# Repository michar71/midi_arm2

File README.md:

# midi_arm2

## BABOI Update
1) Download .bin Firmware File
1) Power Up BABOI
2) Connect Computer o Phone to BABOI Access Point
3) Go to webapge 192.168.1.1 in browser
4) Select "Update"
5) Select firmware File

##Processing Sketch update
Just copy the .app file in the relase folder to your computer 

## LED's

**Left LED**

Red,Green,Blue -> Boot
Yellow -> Ready for Connection
Green -> Connection initiated

**Right LED**

Off > Not Connected
Red > Pause
Green > Live
Blue > Acc/Gyro Cal
Cyan > Mag Cal
Magenta > Button Cal
White > Glove Tension Strip Cal

## Buttons

**Left**

CTRL-Button
Short Press > Live/Pause Toggle
Long Press > Gyro/Accelerometer Calibration
Very Long Press > Mag Calibration

**Front**

A-Button

**Right**

B-Button

## Calibration
- Best Way to calibrate is from the webpage
- Buttons might not work correctly initially. Calibrate from Webpage...
- Gyro/Accelerometer Calibration can be triggered both by 3 sec button press or webpage.
- Button/Mag calibration can only be triggered from webpage.
- If in doubt reset settings from webpage... (That will force a button recalibration on next start...)

## Network
- Enable Network support in App
- Connect computer to "BABOI" access point
- Web Page is available at 192.168.1.1
- VPN/Firewall might enterfere. Traffic is on Port 2255. Connection is established via Broadcast, then communication switches to unicast.

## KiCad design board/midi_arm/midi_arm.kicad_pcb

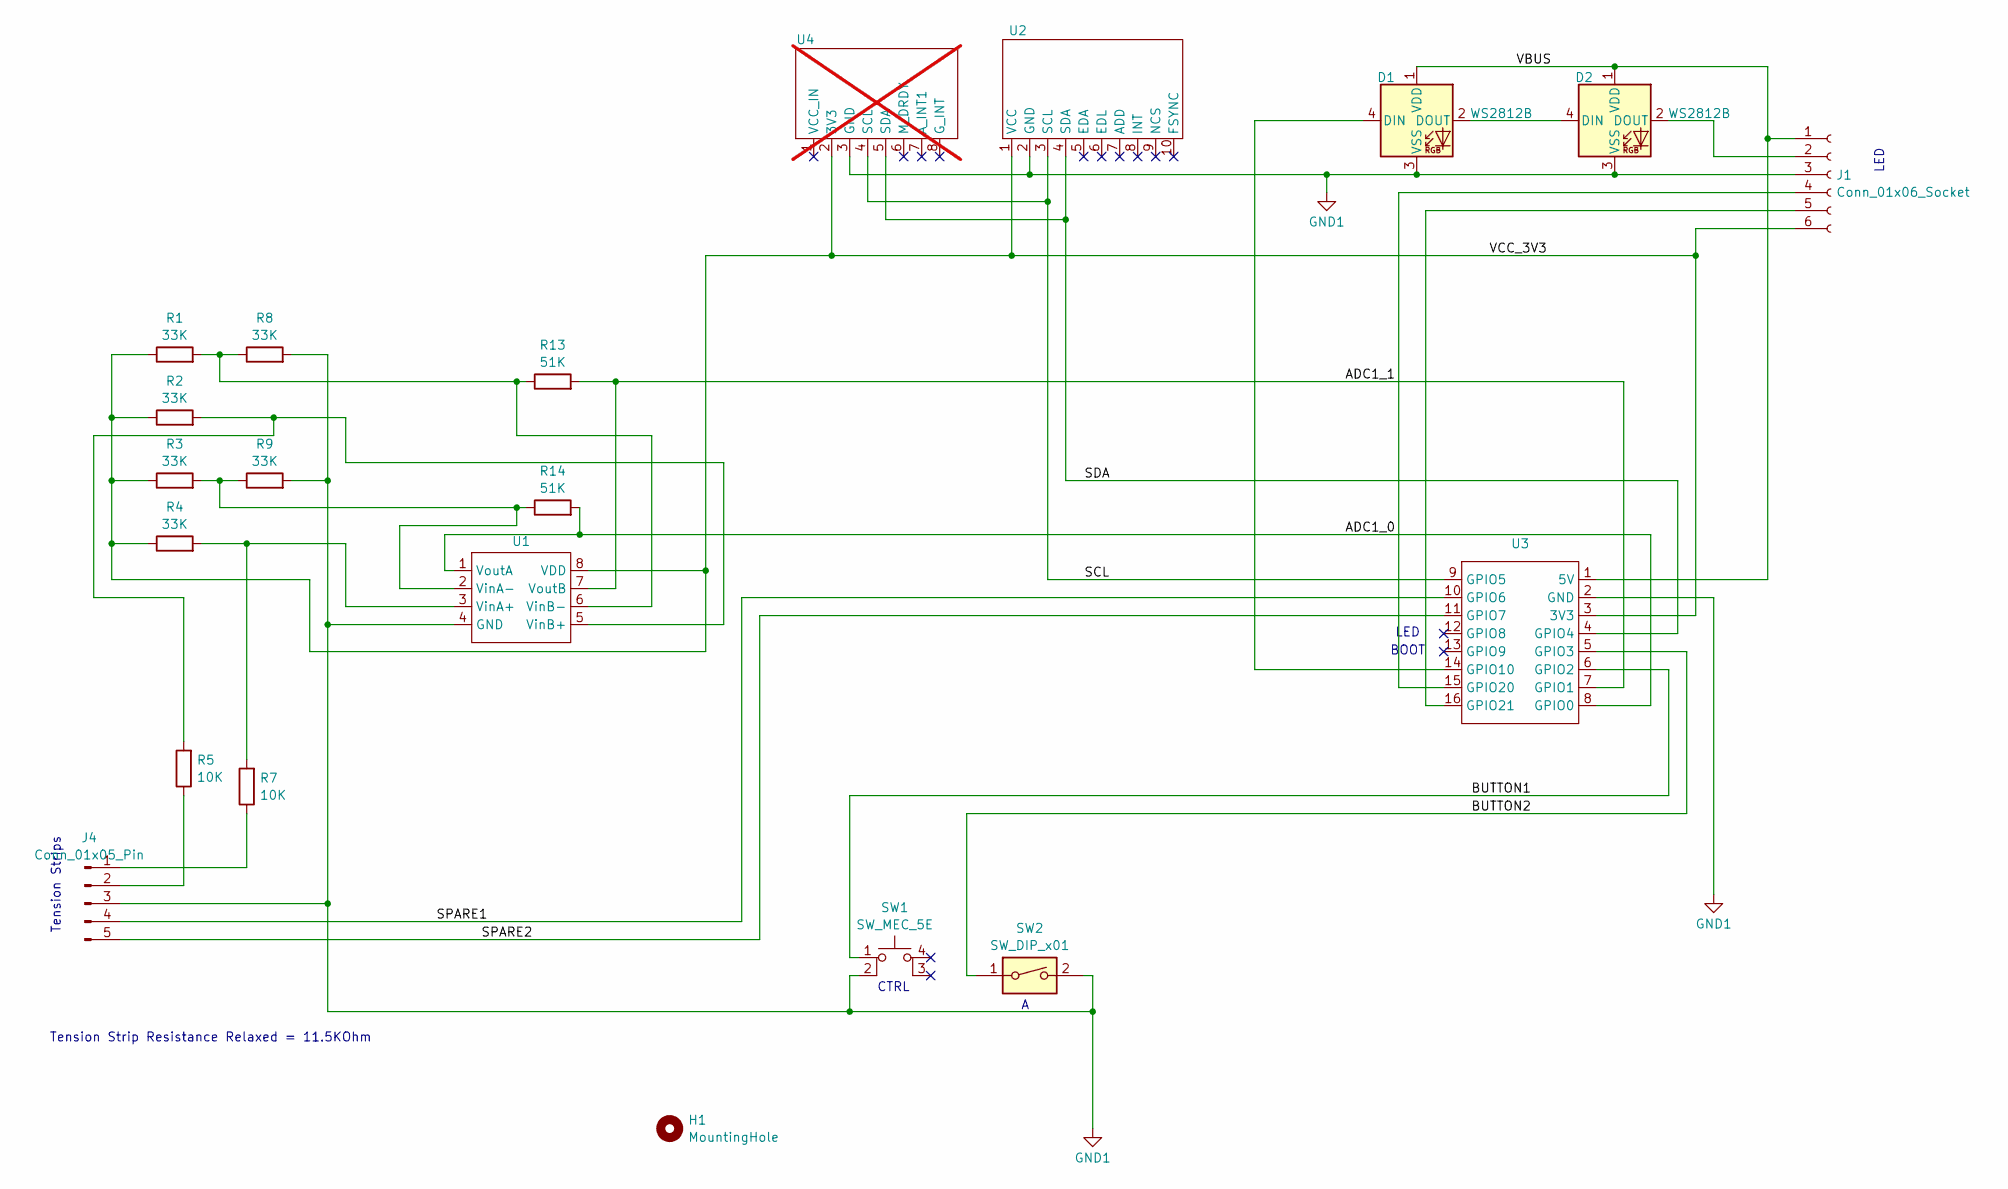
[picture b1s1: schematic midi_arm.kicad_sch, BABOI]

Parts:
D1, D2: WS2812B; LED_WS2812B_PLCC4_5.0x5.0mm_P3.2mm
H1: MountingHole; MountingHole_2mm
J1: Conn_01x06_Socket; PinHeader_1x06_P2.54mm_Vertical
J4: Conn_01x05_Pin; PinHeader_1x05_P2.54mm_Vertical
R1, R2, R3, R4, R8, R9: 33K; R_0805_2012Metric_Pad1.20x1.40mm_HandSolder
R5, R7: 10K; R_0805_2012Metric_Pad1.20x1.40mm_HandSolder
R13, R14: 51K; R_0805_2012Metric_Pad1.20x1.40mm_HandSolder
SW1: SW_MEC_5E; SW_Push_SMD
SW2: SW_DIP_x01; SW_Push_SPST_NO_Alps_SKRK
U1: SOIC-8_3.9x4.9mm_P1.27mm
U2: 9250_MOD
U3: ESP32-C3_SuperMini
U4: GY-85; not fitted

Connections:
/ADC1_0: R14.2, U1.1 (VoutA), U3.8 (GPIO0)
/ADC1_1: R13.2, U1.7 (VoutB), U3.7 (GPIO1)
/BUTTON1: SW1.1, U3.6 (GPIO2)
/BUTTON2: SW2.1, U3.5 (GPIO3)
/SCL: U2.3 (SCL), U3.9 (GPIO5), U4.4 (SCL)
/SDA: U2.4 (SDA), U3.4 (GPIO4), U4.5 (SDA)
/SPARE1: J4.4, U3.10 (GPIO6)
/SPARE2: J4.5, U3.11 (GPIO7)
/VBUS: D1.1 (VDD), D2.1 (VDD), J1.1, U3.1 (5V)
/VCC_3V3: J1.6, R1.1, R2.1, R3.1, R4.1, U1.8 (VDD), U2.1 (VCC), U3.3 (3V3), U4.2 (3V3)
GND1: D1.3 (VSS), D2.3 (VSS), J1.3, J4.3, R8.2, R9.2, SW1.2, SW2.2, U1.4 (GND), U2.2 (GND), U3.2 (GND), U4.3 (GND)
unnamed: D1.4 (DIN), U3.14 (GPIO10)
unnamed: D1.2 (DOUT), D2.4 (DIN)
unnamed: D2.2 (DOUT), J1.2
unnamed: J1.4, U3.15 (GPIO20)
unnamed: J1.5, U3.16 (GPIO21)
unnamed: J4.1, R7.1
unnamed: J4.2, R5.1
unnamed: R4.2, R7.2, U1.3 (VinA+)
unnamed: R3.2, R9.1, R14.1, U1.2 (VinA-)
unnamed: R2.2, R5.2, U1.5 (VinB+)
unnamed: R1.2, R8.1, R13.1, U1.6 (VinB-)

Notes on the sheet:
LED
Tension Strip Resistance Relaxed = 11.5KOhm
CTRL
Tension Strips
BOOT

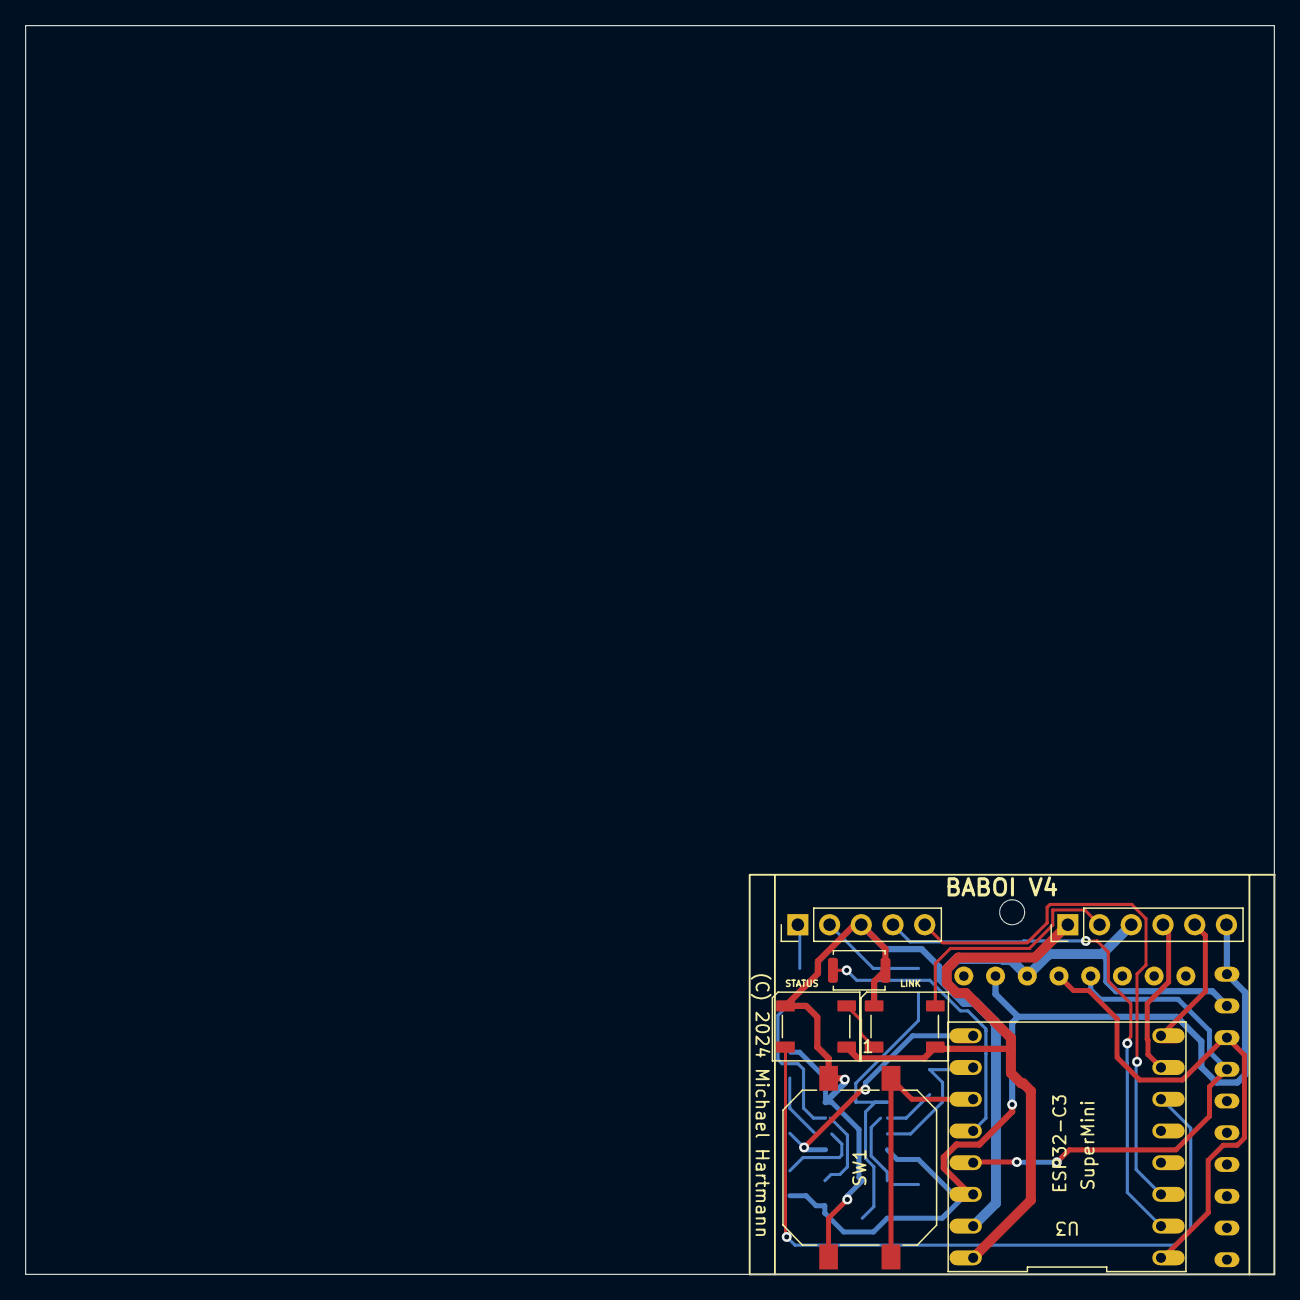
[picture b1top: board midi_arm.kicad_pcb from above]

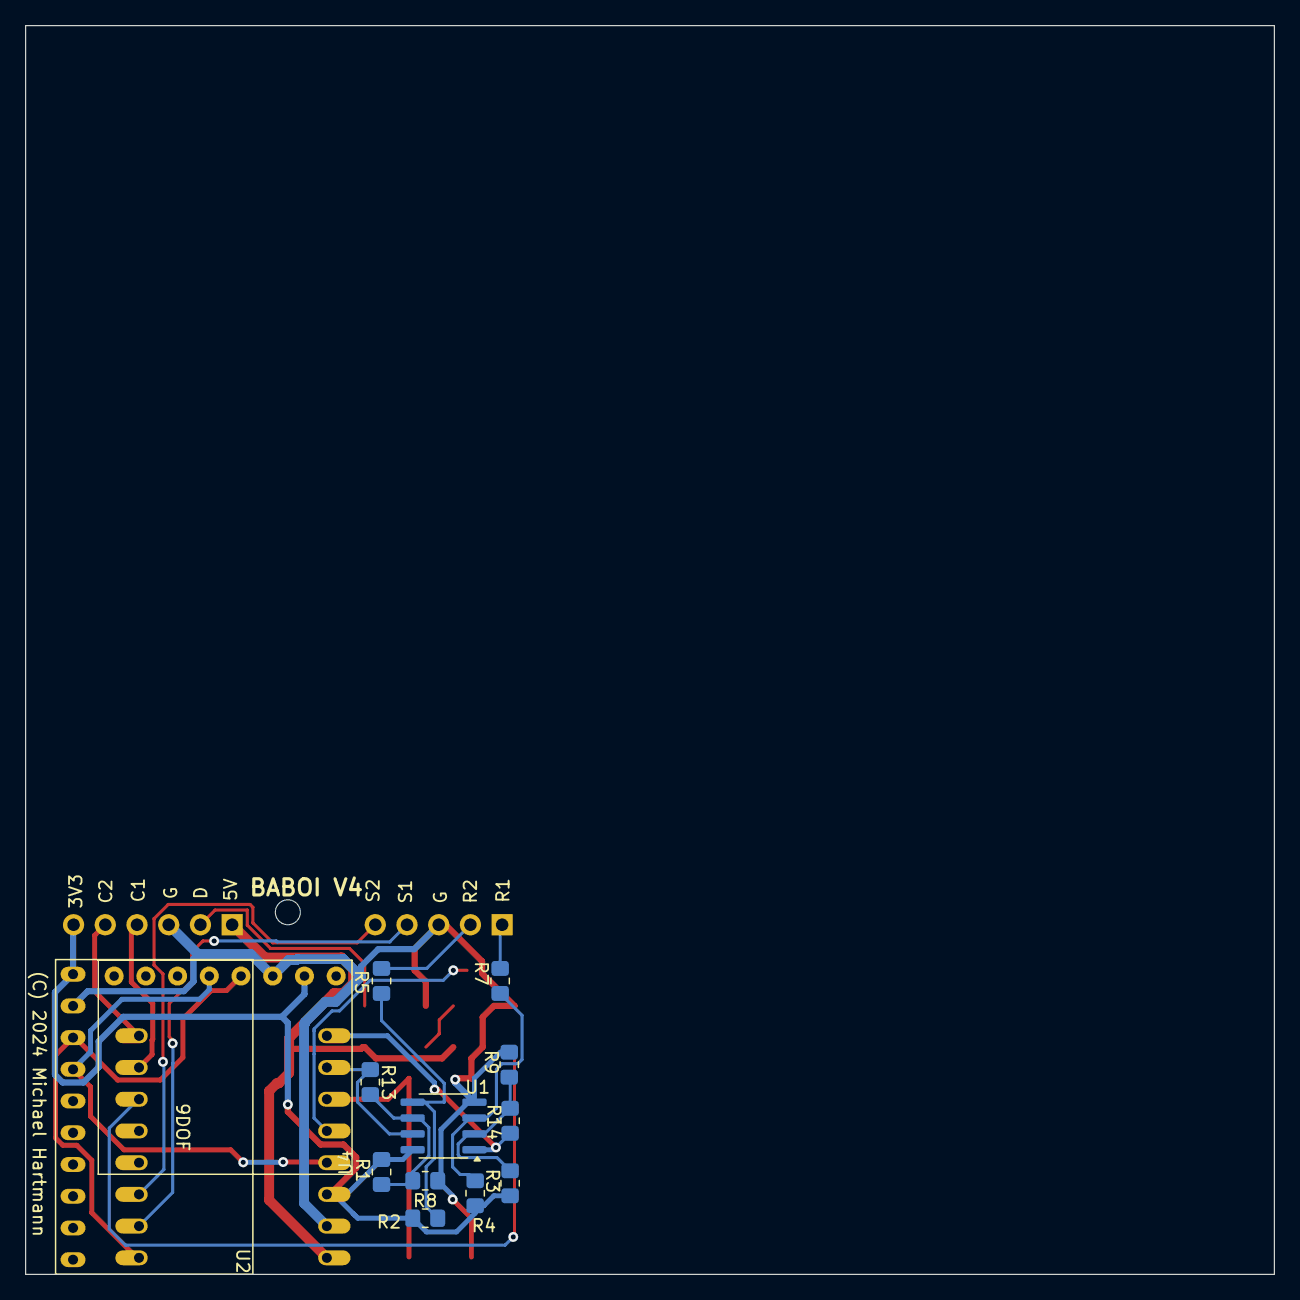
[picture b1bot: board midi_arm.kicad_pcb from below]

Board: 2 copper layers, 100.0 x 100.0 mm, 21 parts (13 on the bottom side), 22 nets.

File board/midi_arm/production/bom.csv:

Designator,Footprint,Quantity,Value,LCSC Part #
"D1_6, D1_5, D1_4, D1_3, D1_2, D1, D2_6, D2_5, D2_4, D2_3, D2_2, D2",LED_WS2812B_PLCC4_5.0x5.0mm_P3.2mm,12,WS2812B,
"J1_6, J1_5, J1_4, J1_3, J1_2, J1",PinHeader_1x06_P2.54mm_Vertical,6,Conn_01x06_Socket,
"J4_6, J4_5, J4_4, J4_3, J4_2, J4",PinHeader_1x05_P2.54mm_Vertical,6,Conn_01x05_Pin,
"R1_6, R1_5, R1_4, R1_3, R1_2, R1, R2_6, R2_5, R2_4, R2_3, R2_2, R2, R3_6, R3_5, R3_4, R3_3, R3_2, R3, R4_6, R4_5, R4_4, R4_3, R4_2, R4, R8_6, R8_5, R8_4, R8_3, R8_2, R8, R9_6, R9_5, R9_4, R9_3, R9_2, R9",0805,36,33K,
"R13_6, R13_5, R13_4, R13_3, R13_2, R13, R14_6, R14_5, R14_4, R14_3, R14_2, R14",0805,12,51K,
"R5_6, R5_5, R5_4, R5_3, R5_2, R5, R7_6, R7_5, R7_4, R7_3, R7_2, R7",0805,12,10K,
"SW1_6, SW1_5, SW1_4, SW1_3, SW1_2, SW1",SW_Push_SMD,6,SW_MEC_5E,
"SW2_6, SW2_5, SW2_4, SW2_3, SW2_2, SW2",SW_Push_SPST_NO_Alps_SKRK,6,SW_DIP_x01,
"U1_6, U1_5, U1_4, U1_3, U1_2, U1",SOIC-8_3.9x4.9mm_P1.27mm,6,~,
"U2_6, U2_5, U2_4, U2_3, U2_2, U2",9250_MOD,6,~,
"U3_6, U3_5, U3_4, U3_3, U3_2, U3",ESP32-C3_SuperMini,6,~,
"U4_6, U4_5, U4_4, U4_3, U4_2, U4",GY-85,6,~,

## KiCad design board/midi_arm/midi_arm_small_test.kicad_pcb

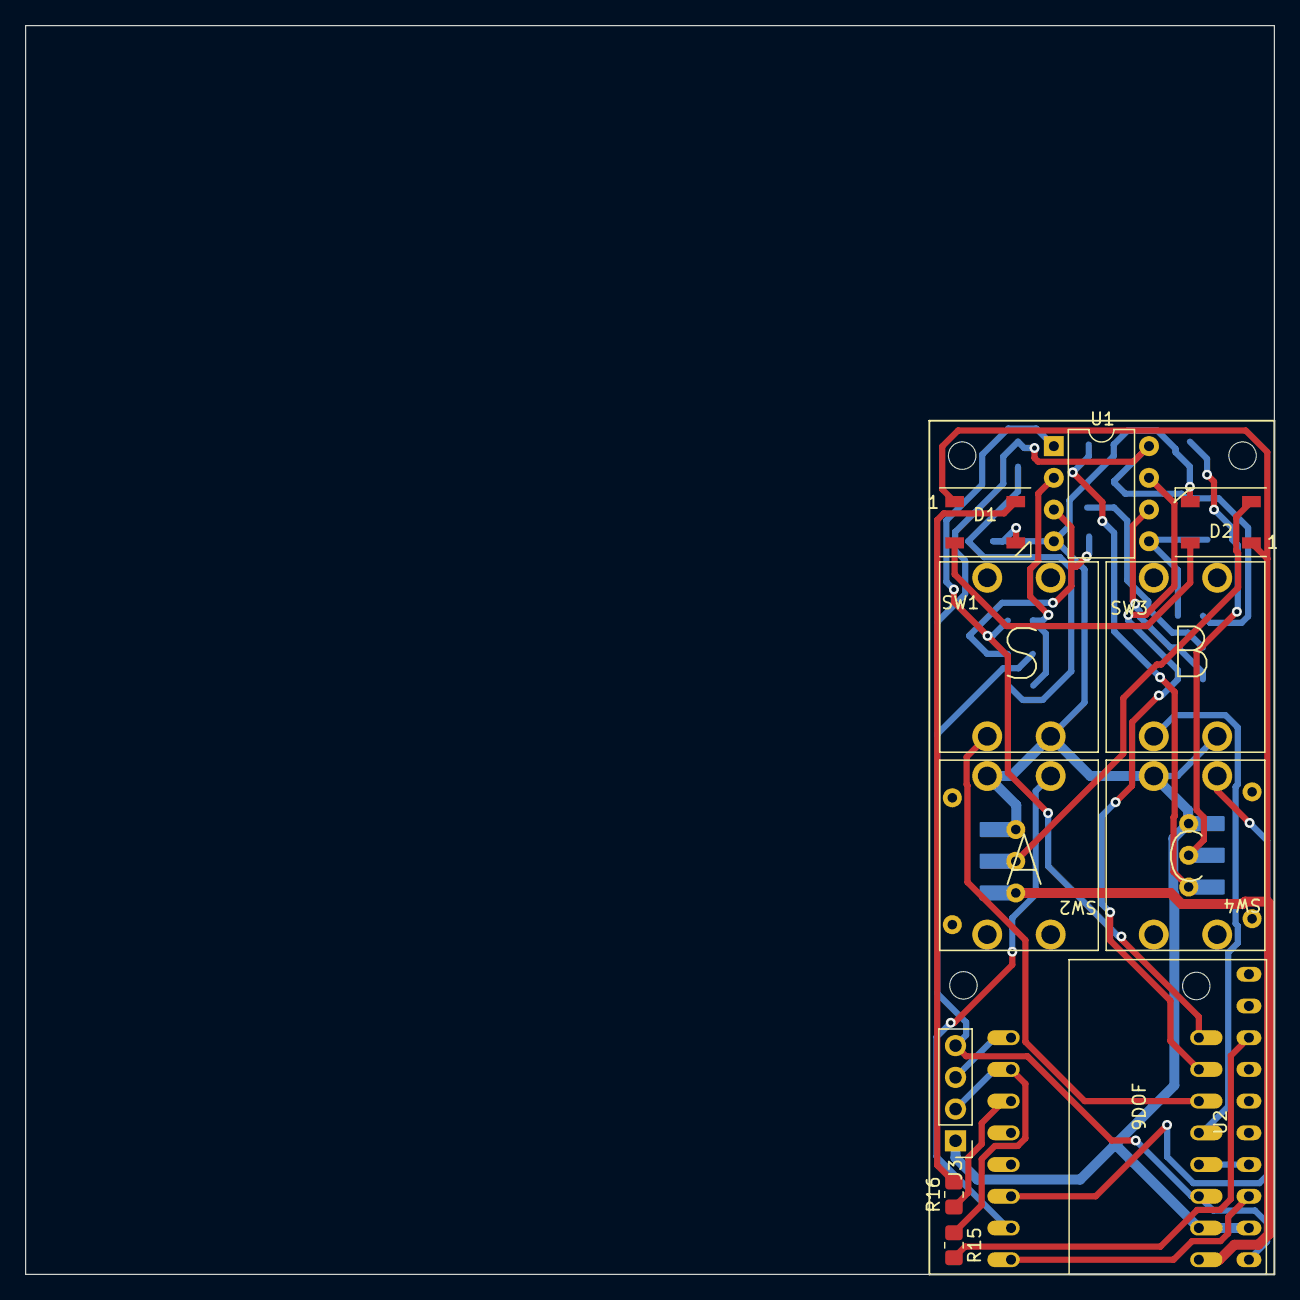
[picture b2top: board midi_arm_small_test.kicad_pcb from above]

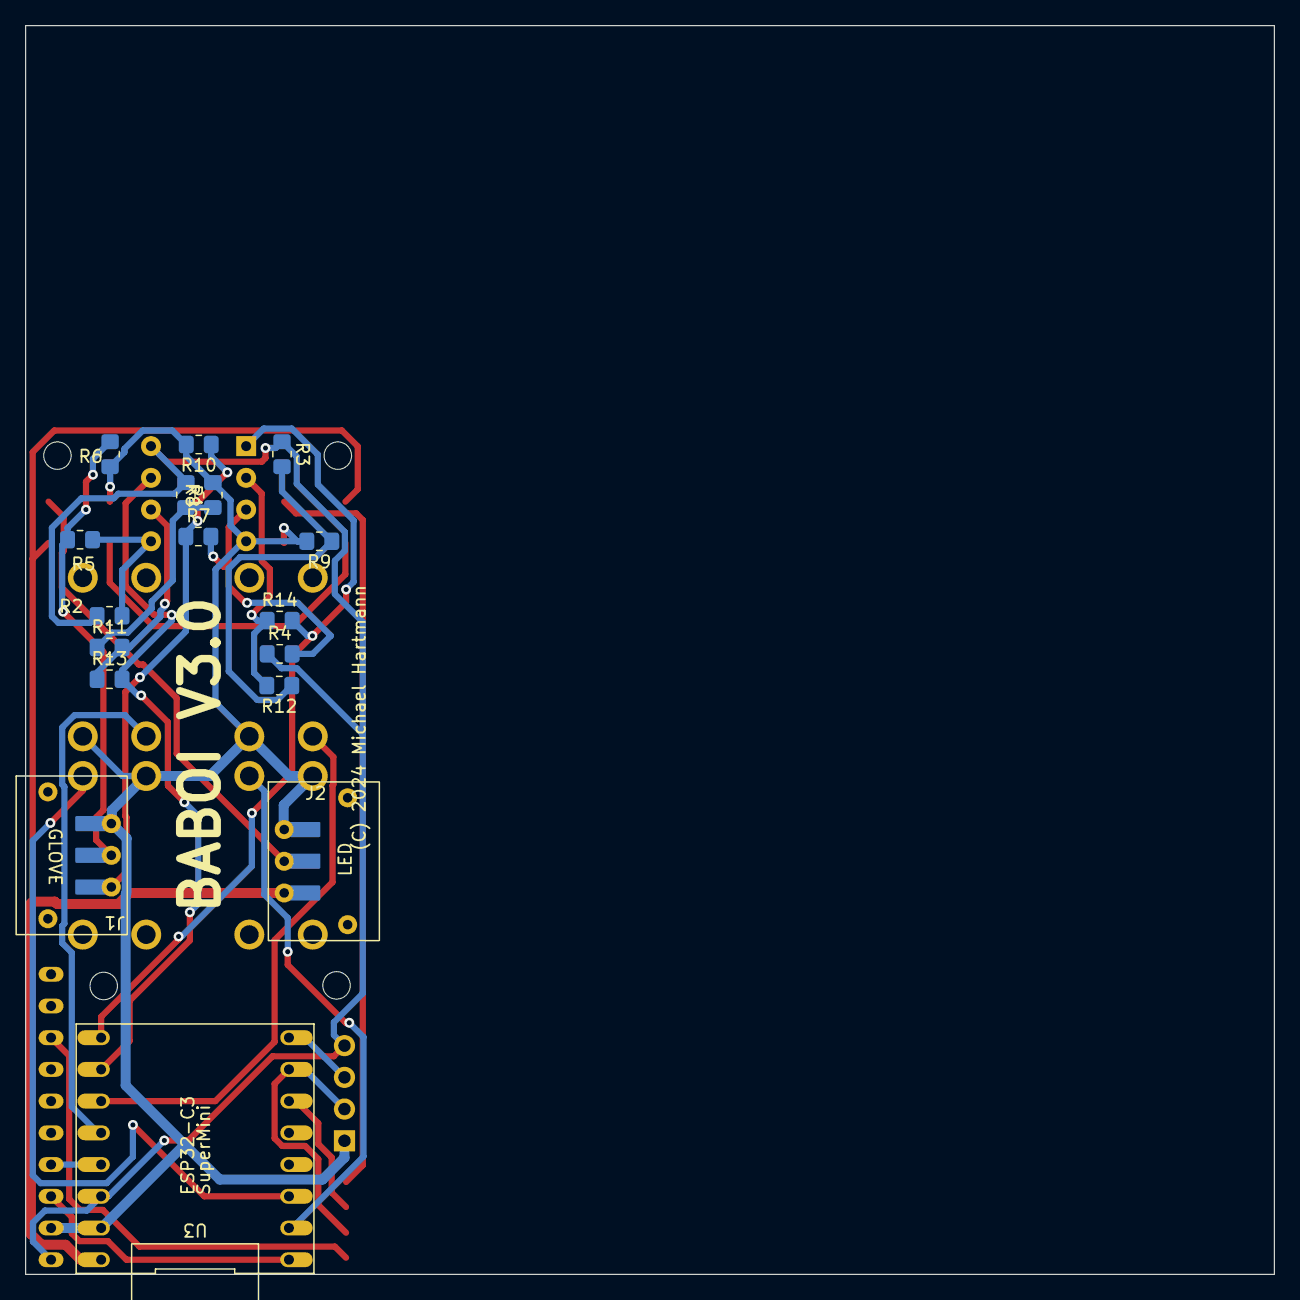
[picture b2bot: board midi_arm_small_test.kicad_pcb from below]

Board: 2 copper layers, 100.0 x 100.0 mm, 32 parts (17 on the bottom side), 26 nets.

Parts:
D1, D2: WS2812B; LED_WS2812B_PLCC4_5.0x5.0mm_P3.2mm
H1, H2, H3, H4: MountingHole; MountingHole_2.2mm_M2
J1, J2: Conn_01x03_Pin; LED_conn
J3: Conn_01x04_Pin; PinHeader_1x04_P2.54mm_Vertical
R1, R3: 2.4k; R_0805_2012Metric_Pad1.20x1.40mm_HandSolder
R2, R4: 5.1k; R_0805_2012Metric_Pad1.20x1.40mm_HandSolder
R5, R6, R7, R8, R9, R10, R11, R12: 3.3k; R_0805_2012Metric_Pad1.20x1.40mm_HandSolder
R13, R14, R15, R16: 24k; R_0805_2012Metric_Pad1.20x1.40mm_HandSolder
SW1, SW2, SW3, SW4: SW_MEC_5E; switch_Simple
U1: DIP-8_W7.62mm
U2: 9250_MOD
U3: ESP32-C3_SuperMini

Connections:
/ADC1_0: R14.2, U1.1 (VoutA), U3.8 (GPIO0)
/ADC1_1: R13.2, U1.7 (VoutB), U3.7 (GPIO1)
/BUTTON1: SW1.2, U3.6 (GPIO2)
/BUTTON2: SW3.2, U3.5 (GPIO3)
/BUTTON3: SW2.2, U3.10 (GPIO6)
/BUTTON4: SW4.2, U3.11 (GPIO7)
/SCL: U2.3 (SCL), U3.9 (GPIO5)
/SDA: U2.4 (SDA), U3.4 (GPIO4)
/VBUS: D1.1 (VDD), D2.1 (VDD), J2.3, U3.1 (5V)
/VCC_3V3: J3.4, R1.1, R2.1, R3.1, R4.1, U1.8 (VDD), U2.1 (VCC), U3.3 (3V3)
GND1: D1.3 (VSS), D2.3 (VSS), J1.3, J2.1, J3.1, R6.2, R8.2, R9.2, R10.2, SW1.3 (K), SW2.3 (K), SW3.3 (K), SW4.3 (K), U1.4 (GND), U2.2 (GND), U3.2 (GND)
unnamed: D1.4 (DIN), R16.2
unnamed: D1.2 (DOUT), D2.4 (DIN)
unnamed: D2.2 (DOUT), J2.2
unnamed: J1.1, R7.1, R10.1
unnamed: J1.2, R5.1, R6.1
unnamed: J3.2, R15.1, U3.15 (GPIO20)
unnamed: J3.3, U3.16 (GPIO21)
unnamed: R1.2, R8.1, R11.1
unnamed: R3.2, R9.1, R12.1
unnamed: R4.2, R7.2, U1.3 (VinA+)
unnamed: R12.2, R14.1, U1.2 (VinA-)
unnamed: R2.2, R5.2, U1.5 (VinB+)
unnamed: R11.2, R13.1, U1.6 (VinB-)
unnamed: R15.2, U2.8 (INT)
unnamed: R16.1, U3.14 (GPIO10)

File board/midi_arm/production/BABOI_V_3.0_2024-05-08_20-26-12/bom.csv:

Designator,Footprint,Quantity,Value,LCSC Part #
"D1_3, D1_2, D1, D2_3, D2_2, D2",LED_WS2812B_PLCC4_5.0x5.0mm_P3.2mm,6,WS2812B,
"H1_3, H1_2, H1, H2_3, H2_2, H2, H3_3, H3_2, H3, H4_3, H4_2, H4",MountingHole_2.2mm_M2,12,MountingHole,
"J1_3, J1_2, J1, J2_3, J2_2, J2",LED_conn,6,Conn_01x03_Pin,
"J3_3, J3_2, J3",PinHeader_1x04_P2.54mm_Vertical,3,Conn_01x04_Pin,
"R1_3, R1_2, R1, R3_3, R3_2, R3",0805,6,2.4k,
"R10_3, R10_2, R10, R11_3, R11_2, R11, R12_3, R12_2, R12, R5_3, R5_2, R5, R6_3, R6_2, R6, R7_3, R7_2, R7, R8_3, R8_2, R8, R9_3, R9_2, R9",0805,24,3.3k,
"R13_3, R13_2, R13, R14_3, R14_2, R14, R15_3, R15_2, R15, R16_3, R16_2, R16",0805,12,24k,
"R2_3, R2_2, R2, R4_3, R4_2, R4",0805,6,5.1k,
"SW1_3, SW1_2, SW1, SW2_3, SW2_2, SW2, SW3_3, SW3_2, SW3, SW4_3, SW4_2, SW4",switch_Simple,12,SW_MEC_5E,
"U1_3, U1_2, U1",DIP-8_W7.62mm,3,~,
"U2_3, U2_2, U2",9250_MOD,3,~,
"U3_3, U3_2, U3",ESP32-C3_SuperMini,3,~,

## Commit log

2023-09-25 Lots of updates
2023-09-27 New CAD, new Code New everyting
2023-09-28 Readme Update
2023-10-06 Code Cleanup and refactoring
2023-10-13 Now with wierless data support....
2023-10-27 Wifi Working
    Code Refactoring
    Wifi Working
2023-11-01 Glove-Integration
2023-11-02 Fix ADC sampling Rate issue
2023-11-03 Fix no-glkove case
2023-11-03 Update arm_processing.pde
    Make lights work via Artnet
2023-11-04 fix minor issues
2023-11-05 fine-tuning
2023-11-05 release 1.2
2023-11-07 Add Network on/off option
2023-11-13 Inbetween step to resolving zero crossing problem.
    Alllow sensor windup to resolve 0-crossing issue.
    Fix issues with out-of-bounds ADC values for Glove.
2023-11-15 Remove crossover detection, allow for sensor windup
2023-11-21 Netywork integration update
    mDNS (baboi.local)
    WifiManager integration
    Better web page
    Correct Broadcast vs Unicast Implementation
    DMX Light integration
2023-12-01 Analog amp sim
2023-12-05 analog sim update
2023-12-12 BABOI 2.0 Board
2023-12-12 Board Update
2023-12-14 Baboi V 2.0
    Support For ADC/glove
2023-12-15 Add support for touchpads vs buttons
2023-12-16 Update Processing scetch
2023-12-16 Sync up settings
2023-12-22 Baboi 2 tested
2023-12-27 adc advancements
2023-12-28 LED Integration
2024-01-05 Refactor Procerssing sketch
    Refactor sketch into classes
2024-01-05 code cleanup
2024-01-26 fixes
2024-05-24 HW Version 3 Support
2024-05-26 Bugfixes
2024-05-26 Add Heartbeat/Setup from main app
2024-05-27 Update cal parameter, add glove filter
2024-07-22 Board 3.5 and code cleanup
    Mini version of Baboi
    Remove Tension Strip option 3/4
    Remove Option for Touch pads
    Move light control to host software
2024-07-23 Bug fixes
2024-07-23 Protocol cleanup
2024-08-05 Add Led FX, absolute direction calibration, Arrow 3D
2024-08-07 Update arrow.mtl
    Fancier Arrow colors....
2024-08-22 nicer arrow
2024-10-05 Support for alternate MCU
2024-10-05 cleanup
2024-10-17 rev 4 board
2024-10-29 Adding latest PCB, adding new settings to override midi bus/uart
2024-11-07 Code Cleanup and Gyro fixes for GY_85
2025-01-22 Add support for hand detection/add arrow
2025-01-23 executable
2025-01-23 Fix Number Display
2025-01-23 Fix range with endless Numberspace
2025-01-25 minor bug fixes
2025-04-29 General Improvements
    - Faster protocol negotiation
    - Add Extra step to start data flow for better syncronisation
    - Add Raw and filtered Data logging
    - Rename Processing project to BAB01

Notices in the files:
board/midi_arm/midi_arm.kicad_pcb:
(C) 2024 Michael Hartmann
